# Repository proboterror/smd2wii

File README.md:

# SMD2Wii
SMD2Wii - adapter for Sega Mega Drive controller to Wii remote.

Adapter emulates Wii Classic Controller with Sega Mega Drive / Genesis 3/6-button controller and can be used with homebrew emulators like Genesis Plus GX and selected Wii Virtual Console Games.<br>
Work not confirmed for NES Classic Mini / SNES Classic Mini.

The goal is to connect SMD 6-button controller to Wii as cheap and simple as possible.<br>
For NES / SNES emulators excellent Nintendo Classic Mini Controller / Nintendo SNES Classic Mini Controller suggested.

Project based on Cluster's [nes2wii](https://github.com/ClusterM/nes2wii) project with following changes:
* Controller replaced with simpler / cheaper ATmega8A
* Deleted all other platforms and second SMD pad support from source code and schematics
* New smaller PCB
* Fixed SMD 6-button pad state query errors
* KiCad 7.0 schematic and PCB sources added

## Schematics

Board:<br>

Assembled board preview without Wiimote connector:

## Fuses 

[Bits configuration](images/fuses.png)

* Low fuse: 0xC4
* High fuse: 0xD9

# Compiling from source
Windows:<br>
Install WinAVR-20100110-install.exe<br>
make all<br>

CH341A programmer and NeoProgrammer V2.2 software can be used for firmware .hex flashing.

## Tested with

* ATmega8A-U, 8MHz
* Third party 6-buttons Sega Mega Drive controller with Mode button ("Retro Genesis 16 Bit ACSg11")
* Software: Genesis Plus GX, FCE Ultra GX, WiiMednafen, RetroArch

## Modes

There are three modes for controller d-pad:
* Mode #1 - d-pad works as left analog stick and d-pad on classic controller at the same time
* Mode #2 - d-pad works as left analog stick only
* Mode #3 - d-pad works as d-pad only

Mode 1 selected by default.

You can hold Start+B+C for a few seconds to change mode. Red led will blink 1/2/3 times indicating new mode.

## Bill of materials
* ATMEGA8A-U TQFP32
* DB9 PCB Connector Angle (DSUB-9 Male Horizontal P2.77x2.84mm Edge Pin Offset 7.70mm Mounting Holes Offset 9.12mm)
* Wii controller 6 Pin 90 degree male connector
* SMD 1206 Resistor 2.2k(222) x3
* SMD 1206 Capacitor 0.1(104) uF x1
* (only for programming) Connector PinHeader 2.54mm 1x06 Vertical
* (optional) Electrolytic Capacitor Radial D5.0mm P2.50mm 4.7 uF
* (optional) SMD 1206 Resistor 400 Ohm x2
* (optional) SMD 1206 LED Red x1
* (optional) SMD 1206 LED Green x1

## Notes

### About delays and interrupts
SMD controller polled every 5 ms. Wiimote classic controller query interrupt disabled during the poll (not sure if interrupt is delayed or cancelled).<br>
Worst case scenario additional input delay is about 5-6 ms (or one frame).<br>
Current code:
```c++
void gamepads_query()
{
	_delay_ms(5); // Must be >= 3 to give 6-button controller time to reset

	cli(); // Disable wiimote poll interrupt

	// 8 iterations for read controller state.
	for (b = 0; b < 8; b++)
	{
		_delay_us(2); // Short delay to stabilise outputs in controller.
		...read pad pins
		...invert SELECT pin
	}

	sei(); // Enable interrupt

```
See [gamepads.c](gamepads.c) code comments for more details.
### Buttons mapping
Classic controller to SMD buttons mapping:
```c++
a = smd.c;
b = smd.b;
x = smd.y;
y = smd.a;
l = smd.x;
r = smd.z;
select = smd.mode;
start = smd.start;
```

## Author(s)

Original firmware and schematics for ATMEGA16A:<br>
Alexey 'Cluster' Avdyukhin [https://github.com/ClusterM](https://github.com/ClusterM)<br>
[https://github.com/ClusterM/nes2wii](https://github.com/ClusterM/nes2wii)

Sega MD 6-buttons query code and documentation:<br>
[https://github.com/MickGyver/DaemonBite-Retro-Controllers-USB](https://github.com/MickGyver/DaemonBite-Retro-Controllers-USB)<br>
[https://github.com/jonthysell/SegaController](https://github.com/jonthysell/SegaController)

SMD2Wii modifications:<br>
[probotector](https://github.com/proboterror)

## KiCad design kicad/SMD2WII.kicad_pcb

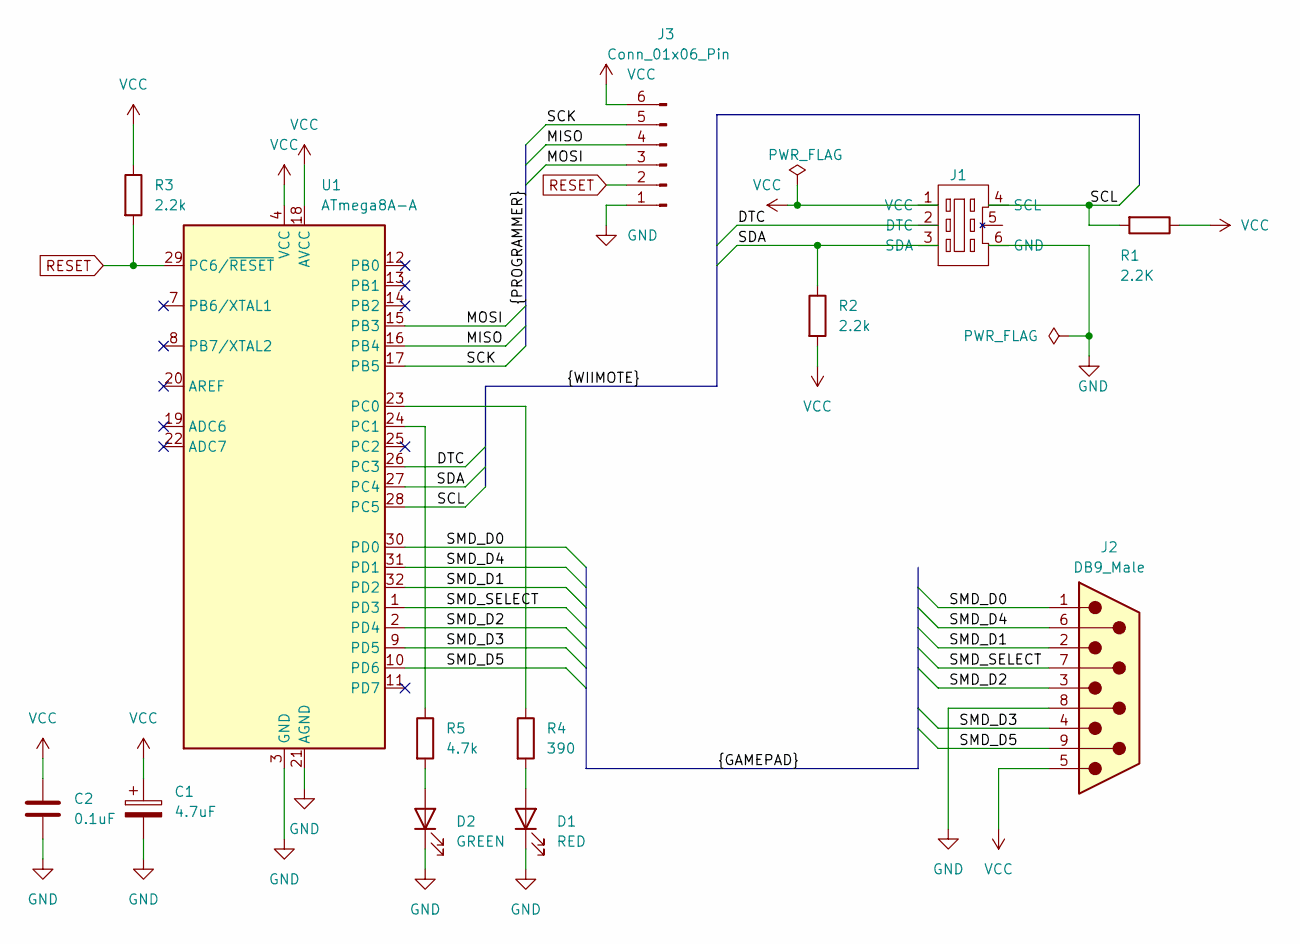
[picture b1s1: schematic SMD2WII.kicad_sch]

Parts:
C1: 4.7uF; CP_Radial_D5.0mm_P2.50mm
C2: 0.1uF; C_1206_3216Metric_Pad1.33x1.80mm_HandSolder
D1: RED; LED_1206_3216Metric_Pad1.42x1.75mm_HandSolder
D2: GREEN; LED_1206_3216Metric_Pad1.42x1.75mm_HandSolder
J1: Wii_Nunchuck_Connector
J2: DB9_Male; DSUB-9_Male_Horizontal_P2.77x2.84mm_EdgePinOffset7.70mm_Hou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
J3: Conn_01x06_Pin; PinHeader_1x06_P2.54mm_Vertical
R1: 2.2K; R_1206_3216Metric_Pad1.30x1.75mm_HandSolder
R2, R3: 2.2k; R_1206_3216Metric_Pad1.30x1.75mm_HandSolder
R4: 390; R_1206_3216Metric_Pad1.30x1.75mm_HandSolder
R5: 4.7k; R_1206_3216Metric_Pad1.30x1.75mm_HandSolder
U1: ATmega8A-A; TQFP-32_7x7mm_P0.8mm

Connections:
/DTC: J1.2 (DTC), U1.26 (PC3)
/MISO: J3.4, U1.16 (PB4)
/MOSI: J3.3, U1.15 (PB3)
/SCK: J3.5, U1.17 (PB5)
/SCL: J1.4 (SCL), R1.2, U1.28 (PC5)
/SDA: J1.3 (SDA), R2.1, U1.27 (PC4)
/SMD_D0: J2.1, U1.30 (PD0)
/SMD_D1: J2.2, U1.32 (PD2)
/SMD_D2: J2.3, U1.2 (PD4)
/SMD_D3: J2.4, U1.9 (PD5)
/SMD_D4: J2.6, U1.31 (PD1)
/SMD_D5: J2.9, U1.10 (PD6)
/SMD_SELECT: J2.7, U1.1 (PD3)
GND: C1.2, C2.2, D1.1 (K), D2.1 (K), J1.6 (GND), J2.8, J3.1, U1.3 (GND), U1.5 (GND), U1.21 (AGND)
unnamed: D1.2 (A), R4.2
unnamed: D2.2 (A), R5.2
unnamed: R4.1, U1.23 (PC0)
unnamed: R5.1, U1.24 (PC1)
RESET: J3.2, R3.2, U1.29 (PC6/~RESET)
VCC: C1.1, C2.1, J1.1 (VCC), J2.5, J3.6, R1.1, R2.2, R3.1, U1.4 (VCC), U1.6 (VCC), U1.18 (AVCC)

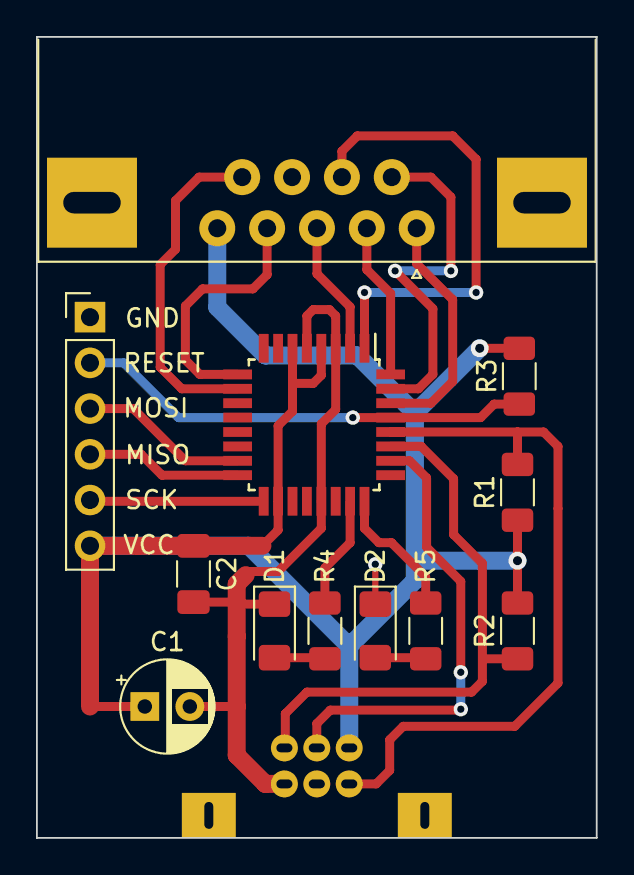
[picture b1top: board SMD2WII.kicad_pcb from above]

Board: 2 copper layers, 31.1 x 44.5 mm, 13 parts (0 on the bottom side), 20 nets.

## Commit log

2023-11-15 Fixed SMD 6-pad reading and detection. Add alternate gamepads_query implementation. Extended comments.
2023-11-15 Fixed 6-buttons SMD gamepad query gliches: wiimote state query interrups breaks SMD 6-button controller state read timings, so disable interrupts before read cycle.
2023-11-15 Remove redundant delay out of main() loop.
2023-11-15 Set d-pad mode as d-pad only by default.
2023-11-15 Set target controller to ATmega8. Set CPU speed to 8 MHZ.
    Controller fuses:
    * Low fuse: 0xC4
    * High fuse: 0xD9
    Correct pins and ports defines according to new scheme.
    Optimize compiler code for size.
    Note: compiler does not calculate bit operations with constants in compile time.
2023-11-15 Replace include guards with pragma once. Delete unused macro.
2023-11-15 Add KiCad 7 schematic and pcb source.
2023-11-15 Add Gerber files for pcb manufacturing.
2023-11-16 Add compiled ATmega8 firmware .hex. Project name in makefile.
2023-11-16 Add new README.md and supplemental images.
2023-12-15 Swap MISO <=> MOSI.
2023-12-16 Connect RESET to VCC instead of GND.
2023-12-18 Compact PCB.
2023-12-20 Re-use C1 pin for front side GND.
2023-12-24 Revert "Set d-pad mode as d-pad only by default."
    This reverts commit 5238fb1d97f34cc982e6786cec14f2f01e515b09.
2023-12-24 Correct description for switch mode buttons.
2024-01-27 PCB confirmed working. Improved position of decoupling capacitor on PCB. Resistor value for green LED changed from 400 Ohm to 4.7k (YMMV).
2024-02-04 Extended comments.
2024-07-10 DSUB-9 connector oval mounting holes.
2024-07-28 Add fuse bits configuration screenshot.
2024-07-28 Error fixed: UP press registers as UP + Z with 3V power. Enable 2 us delay after SELECT signal change before controller data read according to Genesis Software Manual.
2024-08-05 Update README.md.
